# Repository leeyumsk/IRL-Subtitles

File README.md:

# IRL-Subtitles

Using techniques similar to human perception to localize sounds and speakers.

## Project Details

The final goal of the project is to make AR-Glasses that can display text taken from microphones to be displayed on a heads up display to the user. The system integrates a microphone array, and a camera to localize sound, transcribe speech, and visually present captions on a laptop screen connected to the glasses. This project would ideally be combined with a smart glass display/platform in the future.

## Current State
The current state of the project is that there is no processing that is happening locally on the board, all the data is being streamed over to a computer to be processed and displayed. There are one ESP32-S3 wroom 1U that are being used to get audio and one ESP32-S3 eye that is acting as an AP, camera, and handling the data routing. This is a battery powered data colletion unit.

## Project Structure
The project consists of:
1. [Firmware](#1-firmware)
2. [Software](#2-software)
3. [Hardware](#3-hardware)
4. [Extra Documentation](#4-extra-documentation)

Each is structured into their own folders, and sub groups.

### 1. [Firmware](/Firmware/README.md)
This is the code that is running on the ESP32. Most of the code here is for data collection and transmission. This code has two main parts, one that will go on the arm board and one that goes on the eye. This was made, built, and flashed using vscode. 

#### Requirements
- ESP32 IDF
- Target set to ESP32-S3

### 2. [Software](/Software/README.md)
This is the code that will be run on the computer to process the data that is streamed. Due to time constraints the integration of the audio localization was not included in the OpenCV and speech to text display.

### 3. [Hardware](/Hardware/README.md)
This has both the PBC and KiCad files and the glasses cad models.
The main components are:
1. Arm boards - Holds the power management and mics that collect teh audio data.
2. ESP32S3 eye - Collects the visual data and acts as an access point to route the data.
3. [PowerBoost 1000 Charger](https://www.adafruit.com/product/2465) this handle the battery.
4. Frames - Holds all components in a glasses form to be a wearable design.

#### KiCad
This has the KiCad models that were to produce the boards. That includes the schematics, the PCB files, and gerber files to order the glasses.

#### Onshape
Onshape was used to the frames that the PCBs will fit in on the glasses.

### 4. [Extra Documentation](/Extra%20Documentation/README.md)
This is all the documentation that was created in the testing and researching on creating the glasses. This also has the pin outs that were used on the glasses for reference.

## What the Project could use
1. Faster processing, moving computation on the the board.
2. Better integration between programs, face detect, sound location, and speech to text.
3. Localization of sound implemented. 
4. Battery management within code.
5. Redesign/flip the ports for the eye adapter board be able to connect to eye.

## Helpful Links
https://github.com/espressif/esp-who/tree/master

## References

[ESP-idf examples softAP](https://github.com/espressif/esp-idf/blob/master/examples/wifi/getting_started/softAP/main/softap_example_main.c)

[ESP-idf examples station](https://github.com/espressif/esp-idf/tree/master/examples/wifi/getting_started/station)

[espressif esp-who ESP32-S3-EYE](https://github.com/espressif/esp-who/blob/master/docs/en/get-started/ESP32-S3-EYE_Getting_Started_Guide.md)

[GitHub Doc](https://docs.github.com/en/get-started/writing-on-github/getting-started-with-writing-and-formatting-on-github/basic-writing-and-formatting-syntax#links)

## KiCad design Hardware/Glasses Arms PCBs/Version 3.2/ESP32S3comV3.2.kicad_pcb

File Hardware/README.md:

# Hardware
All of the hardware for the project.

## PCB

The PCB has gone through many revisions before it was eventually ordered and printed. The older version are in previous versions branch.

### Version 3.2
Version 3.2 is tha iteration that is used for this guide, where there in now only one ESP32-S3 on the sides of the frames. This has two spots to place a battery on where the battery WITH LOW BATTERY SHUTOFF to the board and on to use with a socketed BMS designed like the one from adafuit, [PowerBoost 500 Charger](https://www.adafruit.com/product/1944). The adapter for the eye has also change to pass through the audio data to the other board.

Version 3.2

These are the pin out for the arm boards.
|Right| | |Left| | 
| ------------- | ------- | - | ------- | ------------- |
| GPIO 15 | GPIO 13 (WS) | | GND | WS | 
| GPIO 9 | GPIO 14 (SCK) | | 3V3 | SCK| 
| GPIO 10 | GPIO 21 (SD) | | x | x | 
| GPIO 11 | 3V3 | | x | SDin | 
| GPIO 12 | GND | | x | LB3v3 |

Eye Adapter Board pins:
| Top | | | | | |
| ------ | ----- | ----- | ---- | ---- | ---- |
| x | x | LB3v3 | SD | SCK | WS|
| GND | IO46 | IO45 | IO3 | IO0 | 3V3 | 
| Bottom | | | | | |
| IO43 | IO21 | IO44 | IO47 | IO48 | GND |
| X | LB3v3 | SD | SCK | WS | 3V3 | 

In the hardware folder is all the production files that is needed to order the PCBs.

## Frames

The frames are designed to clip together without requiring a trip to the hardware store.
The CAD model is parametrically modeled to assist with personalization.
The CAD work was done in onshape and is publicly available.
https://cad.onshape.com/documents/a7485a7ae3b222abdb51885d/w/8202e3e3be7d45f8a3fb9981/e/ac120f3095f84bb498783c7c

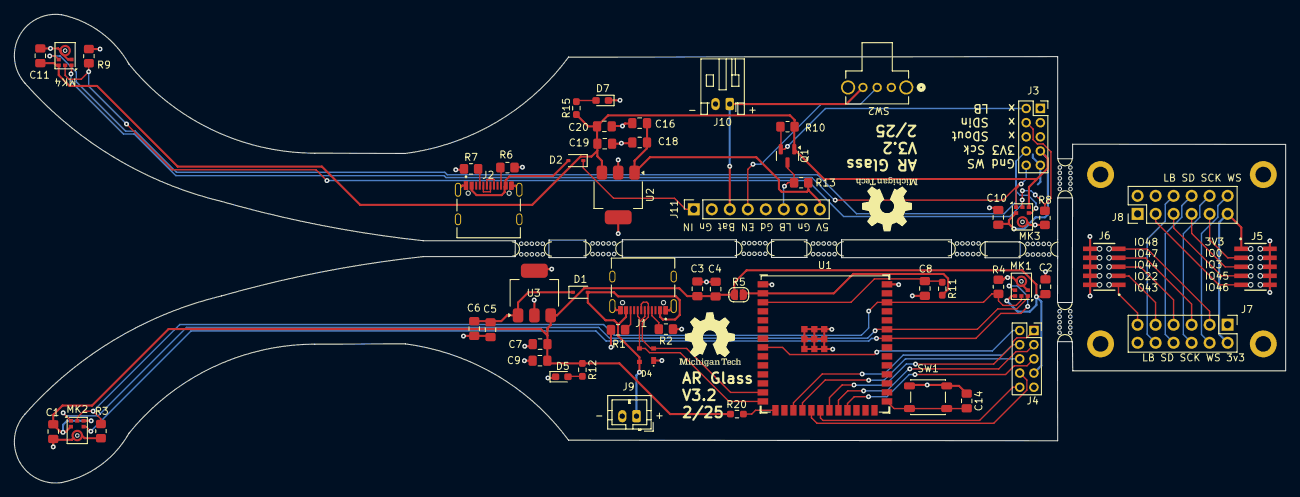
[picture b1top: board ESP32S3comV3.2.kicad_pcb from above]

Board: 2 copper layers, 179.3 x 66.1 mm, 69 parts (0 on the bottom side), 54 nets.

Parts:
C1, C2, C4, C6, C7, C10, C11, C14, C18, C19: 0.1uF; C_0805_2012Metric_Pad1.18x1.45mm_HandSolder
C3, C5, C9, C16, C20: 10uF; C_0805_2012Metric_Pad1.18x1.45mm_HandSolder
C8: 1uF; C_0805_2012Metric_Pad1.18x1.45mm_HandSolder
D1, D2: 1N5819WS; D_SOD-323
D4: PRTR5V0U2X_215; SOT143B
D5, D7: LED; LED_0603_1608Metric_Pad1.05x0.95mm_HandSolder
H1, H2, H3, H4: MountingHole_Pad_MP; MountingHole_2.2mm_M2_DIN965_Pad
J1, J2: USB_C_Receptacle_USB2.0_16P; HRO_TYPE-C-31-M-12
J3, J4: PinSocket_2x05_P2.00mm_Vertical
J5, J6: BD050-10-A-0-0500-L-D; GCT_BD050-10-A-1-0500-L-D
J7, J8: PinHeader_2x06_P2.54mm_Vertical
J9: Conn_02x01; JST_PH_B2B-PH-K_1x02_P2.00mm_Vertical
J10: Conn_01x02; JST_PH_S2B-PH-K_1x02_P2.00mm_Horizontal
J11: Conn_01x08_Socket; PinSocket_1x08_P2.54mm_Vertical
MK1, MK2, MK3, MK4: ICS-43434; InvenSense_ICS-43434-6_3.5x2.65mm
Q1: BSS138; SOT-23
R1, R2, R6, R7: 5.1K; R_0805_2012Metric_Pad1.20x1.40mm_HandSolder
R3, R4, R8, R9: 100k; R_0805_2012Metric_Pad1.20x1.40mm_HandSolder
R5: 0; SolderJumper-2_P1.3mm_Open_RoundedPad1.0x1.5mm
R10, R13: 10k; R_0805_2012Metric_Pad1.20x1.40mm_HandSolder
R11: 10K; R_0603_1608Metric_Pad0.98x0.95mm_HandSolder
R12, R15, R20: 1K; R_0603_1608Metric_Pad0.98x0.95mm_HandSolder
SW1: SW_Push; SW_SPST_PTS647_Sx38
SW2: OS102011MA1QN1; OS102011MA1QN1_CNK
U1: ESP32-S3-WROOM-1U-N8R8; ESP32-S3-WROOM-1U
U2: LT1963AxST-3.3; SOT-223-3_TabPin2
U3: LT1963AEST-3.3; SOT-223-3_TabPin2
mouse-bite-3mm-slot, mouse-bite-3mm-slot-2, mouse-bite-3mm-slot-3, mouse-bite-3mm-slot-4, mouse-bite-3mm-slot-5, mouse-bite-3mm-slot-6, mouse-bite-3mm-slot-7, mouse-bite-3mm-slot-8: 0; mouse-bite-3mm-slot

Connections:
/BoardR/5V: C16.1, C18.1, J11.8, R13.1, U2.1 (IN)
/BoardR/Bat: J10.1, J11.3, SW2.3
/BoardR/CC1: J2.A5 (CC1), R7.2
/BoardR/CC2: J2.B5 (CC2), R6.2
/BoardR/D+: J2.A6 (D+), J2.B6 (D+)
/BoardR/D-: J2.A7 (D-), J2.B7 (D-)
/BoardR/EN: J11.4, SW2.2
/BoardR/LB: J11.6, Q1.3 (D), R13.2
/BoardR/LB3v3: J3.2, Q1.2 (S), R10.2
/BoardR/SCK: J3.8, MK3.4 (SCK), MK4.4 (SCK)
/BoardR/SDin: J3.4, MK3.6 (SD), MK4.6 (SD), R8.1, R9.1
/BoardR/USB: D2.1 (K), J11.1
/BoardR/VBUS: D2.2 (A), J2.A4 (VBUS), J2.A9 (VBUS), J2.B4 (VBUS), J2.B9 (VBUS)
/BoardR/VCC_3V3: C10.1, C11.1, C19.1, C20.1, J3.7, MK3.2 (LR), MK3.5 (VDD), MK4.5 (VDD), Q1.1 (G), R10.1, R15.1, U2.3 (OUT)
/BoardR/WS: J3.10, MK3.1 (WS), MK4.1 (WS)
/CC1: J1.A5 (CC1), R2.2
/CC2: J1.B5 (CC2), R1.2
/CHIP_PU: C8.1, R11.1, U1.3 (EN)
/D+: D4.3, J1.A6 (D+), J1.B6 (D+), U1.14 (IO20)
/D-: D4.2, J1.A7 (D-), J1.B7 (D-), U1.13 (IO19)
/ESP_3V3: R5.2, R11.2, U1.2 (3V3)
/Eye connect/IO0: J5.3, J8.9
/Eye connect/IO3: J5.5, J8.7
/Eye connect/IO21: J6.3, J7.9
/Eye connect/IO43: J6.1, J7.11
/Eye connect/IO44: J6.5, J7.7
/Eye connect/IO45: J5.7, J8.5
/Eye connect/IO46: J5.9, J8.3
/Eye connect/IO47: J6.7, J7.5
/Eye connect/IO48: J6.9, J7.3
/Eye connect/LB: J7.10, J8.6
/Eye connect/SCK1: J7.6, J8.10
/Eye connect/SD1: J7.8, J8.8
/Eye connect/VCC_3V3: J5.1, J7.2, J8.11
/Eye connect/WS1: J7.4, J8.12
/GPIO0: C14.2, SW1.2, U1.27 (IO0)
/GPIO2: MK1.6 (SD), MK2.6 (SD), R3.1, R4.1, U1.38 (IO2)
/GPIO3: R20.1, U1.15 (IO3)
/GPIO9: J4.4, U1.17 (IO9)
/GPIO10: J4.6, U1.18 (IO10)
/GPIO11: J4.8, U1.19 (IO11)
/GPIO12: J4.10, U1.20 (IO12)
/GPIO13: J4.1, U1.21 (IO13)
/GPIO14: J4.3, U1.22 (IO14)
/GPIO15: J4.2, U1.8 (IO15)
/GPIO21: J4.5, U1.23 (IO21)
/GPIO41: MK1.4 (SCK), MK2.4 (SCK), U1.34 (IO41)
/GPIO42: MK1.1 (WS), MK2.1 (WS), U1.35 (IO42)
/VBUS: D1.2 (A), D4.4, J1.A4 (VBUS), J1.A9 (VBUS), J1.B4 (VBUS), J1.B9 (VBUS), J9.1
/VCC_3V3: C1.1, C2.1, C3.1, C4.1, C7.1, C9.1, J4.7, MK1.5 (VDD), MK2.2 (LR), MK2.5 (VDD), R5.1, R12.1, R20.2, U3.3 (OUT)
/VCC_5: C5.1, C6.1, D1.1 (K), U3.1 (IN)
GND: C1.2, C2.2, C3.2, C4.2, C5.2, C6.2, C7.2, C8.2, C9.2, C10.2, C11.2, C14.1, C16.2, C18.2, C19.2, C20.2, D4.1, D5.1 (K), D7.1 (K), J1.A1 (GND), J1.A12 (GND), J1.B1 (GND), J1.B12 (GND), J1.S1 (SHIELD), J2.A1 (GND), J2.A12 (GND), J2.B1 (GND), J2.B12 (GND), J2.S1 (SHIELD), J3.9, J4.9, J5.2, J5.4, J5.6, J5.8, J5.10, J6.2, J6.4, J6.6, J6.8, J6.10, J7.1, J8.1, J9.2, J10.2, J11.2, J11.5, J11.7, MK1.2 (LR), MK1.3 (GND), MK2.3 (GND), MK3.3 (GND), MK4.2 (LR), MK4.3 (GND), R1.1, R2.1, R3.2, R4.2, R6.1, R7.1, R8.2, R9.2, SW1.1, SW2.1, U1.1 (GND), U1.40 (GND), U1.41 (GND), U2.2 (GND), U3.2 (GND)
unnamed: D5.2 (A), R12.2
unnamed: D7.2 (A), R15.2

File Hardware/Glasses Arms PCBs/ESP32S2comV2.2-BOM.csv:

Designator,Footprint,Quantity,Value,LCSC Part #
"C1, C10, C11, C13, C2, C4, C6, C7",0805,8,0.1uF,C49678
"C12, C3, C5, C9",0805,4,10uF,C15850
"C17, C8",0805,2,1uF,C89378
"D1, D2",D_SOD-323,2,1N5819WS,C191023
"D3, D4",SOT143B,2,PRTR5V0U2X_215,C2827688
"D5, D6",0603,2,LED,C2286
"J1, J2",HRO_TYPE-C-31-M-12,2,USB_C_Receptacle_USB2.0_16P,C165948
"J3, J4",PinSocket_2x05_P2.00mm_Vertical,2,Connector_Generic:Conn_02x05_Top_Bottom,C225304
"MK1, MK2, MK3, MK4",InvenSense_ICS-43434-6_3.5x2.65mm,4,ICS-43434,
"MOUSE-BITE-3MM-SLOT, MOUSE-BITE-3MM-SLOT-2, MOUSE-BITE-3MM-SLOT-3, MOUSE-BITE-3MM-SLOT-4, MOUSE-BITE-3MM-SLOT-5, MOUSE-BITE-3MM-SLOT-6",mouse-bite-3mm-slot,6,0,
"R1, R2, R6, R7",0805,4,5.1K,C27834
"R10, R5",SolderJumper-2_P1.3mm_Open_RoundedPad1.0x1.5mm,2,0,
"R11, R13",0603,2,10K,C25804
"R12, R14, R20, R21",0603,4,1K,C21190
"R3, R4, R8, R9",0805,4,100k,C149504
"U1, U8",ESP32-S3-WROOM-1U,2,ESP32-S3-WROOM-1U-N8R8,C2980300
U3,SOT-223-3_TabPin2,1,LT1963AxST-3.3,C459918

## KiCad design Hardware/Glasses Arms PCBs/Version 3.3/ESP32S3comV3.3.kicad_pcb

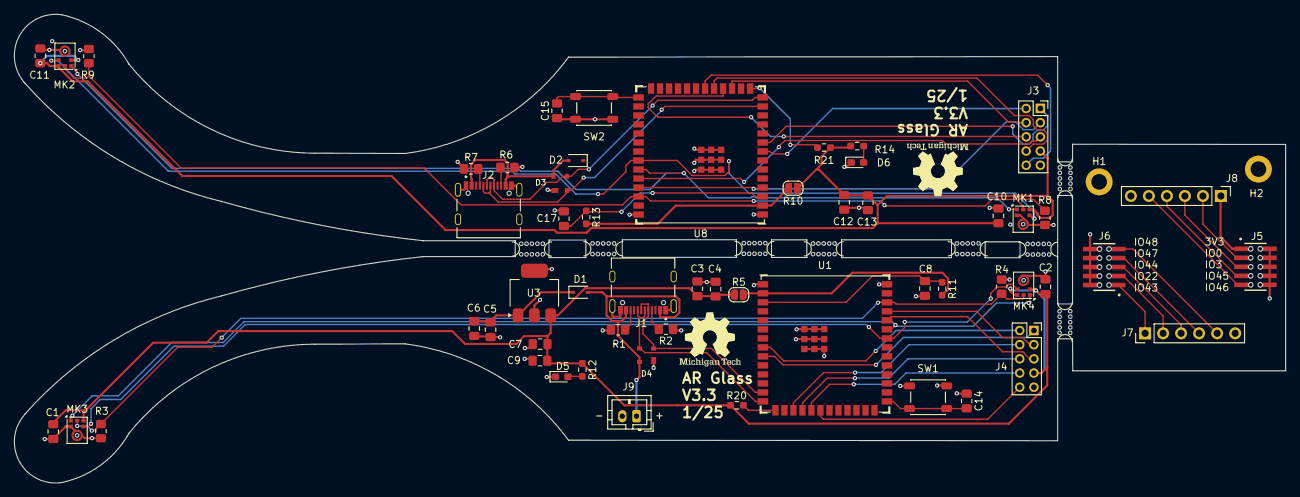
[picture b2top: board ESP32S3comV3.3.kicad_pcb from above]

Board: 2 copper layers, 179.3 x 66.1 mm, 66 parts (0 on the bottom side), 56 nets.

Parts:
C1, C2, C4, C6, C7, C10, C11, C13, C14, C15: 0.1uF; C_0805_2012Metric_Pad1.18x1.45mm_HandSolder
C3, C5, C9, C12: 10uF; C_0805_2012Metric_Pad1.18x1.45mm_HandSolder
C8, C17: 1uF; C_0805_2012Metric_Pad1.18x1.45mm_HandSolder
D1, D2: 1N5819WS; D_SOD-323
D3, D4: PRTR5V0U2X_215; SOT143B
D5, D6: LED; LED_0603_1608Metric_Pad1.05x0.95mm_HandSolder
H1, H2: MountingHole_Pad_MP; MountingHole_2.2mm_M2_DIN965_Pad
J1, J2: USB_C_Receptacle_USB2.0_16P; HRO_TYPE-C-31-M-12
J3, J4: Connector_Generic:Conn_02x05_Top_Bottom; PinSocket_2x05_P2.00mm_Vertical
J5, J6: BD050-10-A-0-0500-L-D; GCT_BD050-10-A-1-0500-L-D
J7, J8: Conn_01x06; PinHeader_1x06_P2.54mm_Vertical
J9: Conn_02x01; JST_PH_B2B-PH-K_1x02_P2.00mm_Vertical
MK1, MK2, MK3, MK4: ICS-43434; InvenSense_ICS-43434-6_3.5x2.65mm
R1, R2, R6, R7: 5.1K; R_0805_2012Metric_Pad1.20x1.40mm_HandSolder
R3, R4, R8, R9: 100k; R_0805_2012Metric_Pad1.20x1.40mm_HandSolder
R5, R10: 0; SolderJumper-2_P1.3mm_Open_RoundedPad1.0x1.5mm
R11, R13: 10K; R_0603_1608Metric_Pad0.98x0.95mm_HandSolder
R12, R14, R20, R21: 1K; R_0603_1608Metric_Pad0.98x0.95mm_HandSolder
SW1, SW2: SW_Push; SW_SPST_PTS647_Sx38
U1, U8: ESP32-S3-WROOM-1U-N8R8; ESP32-S3-WROOM-1U
U3: LT1963AxST-3.3; SOT-223-3_TabPin2
mouse-bite-3mm-slot, mouse-bite-3mm-slot-2, mouse-bite-3mm-slot-3, mouse-bite-3mm-slot-4, mouse-bite-3mm-slot-5, mouse-bite-3mm-slot-6, mouse-bite-3mm-slot-6#2, mouse-bite-3mm-slot-6#3: 0; mouse-bite-3mm-slot

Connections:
/BoardR/CC1: J2.A5 (CC1), R7.2
/BoardR/CC2: J2.B5 (CC2), R6.2
/BoardR/CHIP_PU: C17.1, R13.1, U8.3 (EN)
/BoardR/D+: D3.3, J2.A6 (D+), J2.B6 (D+), U8.14 (IO20)
/BoardR/D-: D3.2, J2.A7 (D-), J2.B7 (D-), U8.13 (IO19)
/BoardR/ESP_3V3: R10.2, R13.2, U8.2 (3V3)
/BoardR/GPIO0: C15.2, SW2.2, U8.27 (IO0)
/BoardR/GPIO2: MK1.6 (SD), MK2.6 (SD), R8.1, R9.1, U8.38 (IO2)
/BoardR/GPIO3: R21.1, U8.15 (IO3)
/BoardR/GPIO9: J3.4, U8.17 (IO9)
/BoardR/GPIO10: J3.6, U8.18 (IO10)
/BoardR/GPIO11: J3.8, U8.19 (IO11)
/BoardR/GPIO12: J3.10, U8.20 (IO12)
/BoardR/GPIO15: J3.2, U8.8 (IO15)
/BoardR/GPIO16: J3.1, U8.9 (IO16)
/BoardR/GPIO41: MK1.4 (SCK), MK2.4 (SCK), U8.34 (IO41)
/BoardR/GPIO42: MK1.1 (WS), MK2.1 (WS), U8.35 (IO42)
/BoardR/RXD0: J3.5, U8.36 (RXD0)
/BoardR/TXD0: J3.3, U8.37 (TXD0)
/BoardR/VBUS: D2.2 (A), D3.4, J2.A4 (VBUS), J2.A9 (VBUS), J2.B4 (VBUS), J2.B9 (VBUS)
/BoardR/VCC_3V3: C10.1, C11.1, C12.1, C13.1, J3.7, MK1.5 (VDD), MK2.2 (LR), MK2.5 (VDD), R10.1, R14.1, R21.2
/CC1: J1.A5 (CC1), R2.2
/CC2: J1.B5 (CC2), R1.2
/CHIP_PU: C8.1, R11.1, U1.3 (EN)
/D+: D4.3, J1.A6 (D+), J1.B6 (D+), U1.14 (IO20)
/D-: D4.2, J1.A7 (D-), J1.B7 (D-), U1.13 (IO19)
/ESP_3V3: R5.2, R11.2, U1.2 (3V3)
/Eye connect/IO0: J5.3, J8.2
/Eye connect/IO3: J5.5, J8.3
/Eye connect/IO21: J6.3, J7.2
/Eye connect/IO43: J6.1, J7.1
/Eye connect/IO44: J6.5, J7.3
/Eye connect/IO45: J5.7, J8.4
/Eye connect/IO46: J5.9, J8.5
/Eye connect/IO47: J6.7, J7.4
/Eye connect/IO48: J6.9, J7.5
/Eye connect/VCC_3V3: J5.1, J8.1
/GPIO0: C14.2, SW1.2, U1.27 (IO0)
/GPIO2: MK3.6 (SD), MK4.6 (SD), R3.1, R4.1, U1.38 (IO2)
/GPIO3: R20.1, U1.15 (IO3)
/GPIO9: J4.4, U1.17 (IO9)
/GPIO10: J4.6, U1.18 (IO10)
/GPIO11: J4.8, U1.19 (IO11)
/GPIO12: J4.10, U1.20 (IO12)
/GPIO15: J4.2, U1.8 (IO15)
/GPIO16: J4.1, U1.9 (IO16)
/GPIO41: MK3.4 (SCK), MK4.4 (SCK), U1.34 (IO41)
/GPIO42: MK3.1 (WS), MK4.1 (WS), U1.35 (IO42)
/RXD0: J4.5, U1.36 (RXD0)
/TXD0: J4.3, U1.37 (TXD0)
/VBUS: D1.2 (A), D4.4, J1.A4 (VBUS), J1.A9 (VBUS), J1.B4 (VBUS), J1.B9 (VBUS), J9.1
/VCC_3V3: C1.1, C2.1, C3.1, C4.1, C7.1, C9.1, J4.7, MK3.5 (VDD), MK4.2 (LR), MK4.5 (VDD), R5.1, R12.1, R20.2, U3.3 (OUT)
/VCC_5: C5.1, C6.1, D1.1 (K), U3.1 (IN)
GND: C1.2, C2.2, C3.2, C4.2, C5.2, C6.2, C7.2, C8.2, C9.2, C10.2, C11.2, C12.2, C13.2, C14.1, C15.1, C17.2, D3.1, D4.1, D5.1 (K), D6.1 (K), J1.A1 (GND), J1.A12 (GND), J1.B1 (GND), J1.B12 (GND), J1.S1 (SHIELD), J2.A1 (GND), J2.A12 (GND), J2.B1 (GND), J2.B12 (GND), J2.S1 (SHIELD), J3.9, J4.9, J5.2, J5.4, J5.6, J5.8, J5.10, J6.2, J6.4, J6.6, J6.8, J6.10, J7.6, J8.6, J9.2, MK1.2 (LR), MK1.3 (GND), MK2.3 (GND), MK3.2 (LR), MK3.3 (GND), MK4.3 (GND), R1.1, R2.1, R3.2, R4.2, R6.1, R7.1, R8.2, R9.2, SW1.1, SW2.1, U1.1 (GND), U1.40 (GND), U1.41 (GND), U3.2 (GND), U8.1 (GND), U8.40 (GND), U8.41 (GND)
unnamed: D5.2 (A), R12.2
unnamed: D6.2 (A), R14.2

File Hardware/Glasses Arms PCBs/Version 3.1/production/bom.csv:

Designator,Footprint,Quantity,Value,LCSC Part #
"C1, C10, C11, C14, C18, C19, C2, C4, C6, C7",0805,10,0.1uF,
"C16, C20, C3, C5, C9",0805,5,10uF,
C8,0805,1,1uF,
"D1, D2",D_SOD-323,2,1N5819WS,
D4,SOT143B,1,PRTR5V0U2X_215,
"D5, D7",0603,2,LED,
"J1, J2",HRO_TYPE-C-31-M-12,2,USB_C_Receptacle_USB2.0_16P,
J10,JST_PH_S2B-PH-K_1x02_P2.00mm_Horizontal,1,Conn_01x02,
J11,PinSocket_1x08_P2.54mm_Vertical,1,Conn_01x08_Socket,
"J3, J4",PinSocket_2x05_P2.00mm_Vertical,2,Connector_Generic:Conn_02x05_Top_Bottom,
"J5, J6",GCT_BD050-10-A-1-0500-L-D,2,BD050-10-A-0-0500-L-D,
"J7, J8",PinHeader_2x06_P2.54mm_Vertical,2,Conn_02x06,
J9,JST_PH_B2B-PH-K_1x02_P2.00mm_Vertical,1,Conn_02x01,
"MK1, MK2, MK5, MK6",MIC_CMM-4030D-261-I2S-TR,4,MSM261S4030H0R,
"MOUSE-BITE-3MM-SLOT, MOUSE-BITE-3MM-SLOT-2, MOUSE-BITE-3MM-SLOT-3, MOUSE-BITE-3MM-SLOT-4, MOUSE-BITE-3MM-SLOT-5, MOUSE-BITE-3MM-SLOT-6, MOUSE-BITE-3MM-SLOT-7, MOUSE-BITE-3MM-SLOT-8",mouse-bite-3mm-slot,8,0,
Q1,SOT-23,1,BSS138,
"R1, R2, R6, R7",0805,4,5.1K,
"R10, R13",0805,2,10k,
R11,0603,1,10K,
"R12, R15, R20",0603,3,1K,
"R3, R4, R8, R9",0805,4,100k,
R5,SolderJumper-2_P1.3mm_Open_RoundedPad1.0x1.5mm,1,0,
SW1,SW_SPST_PTS647_Sx38,1,SW_Push,
SW2,OS102011MA1QN1_CNK,1,OS102011MA1QN1,
U1,ESP32-S3-WROOM-1U,1,ESP32-S3-WROOM-1U-N8R8,
"U2, U3",SOT-223-3_TabPin2,2,LT1963AxST-3.3,

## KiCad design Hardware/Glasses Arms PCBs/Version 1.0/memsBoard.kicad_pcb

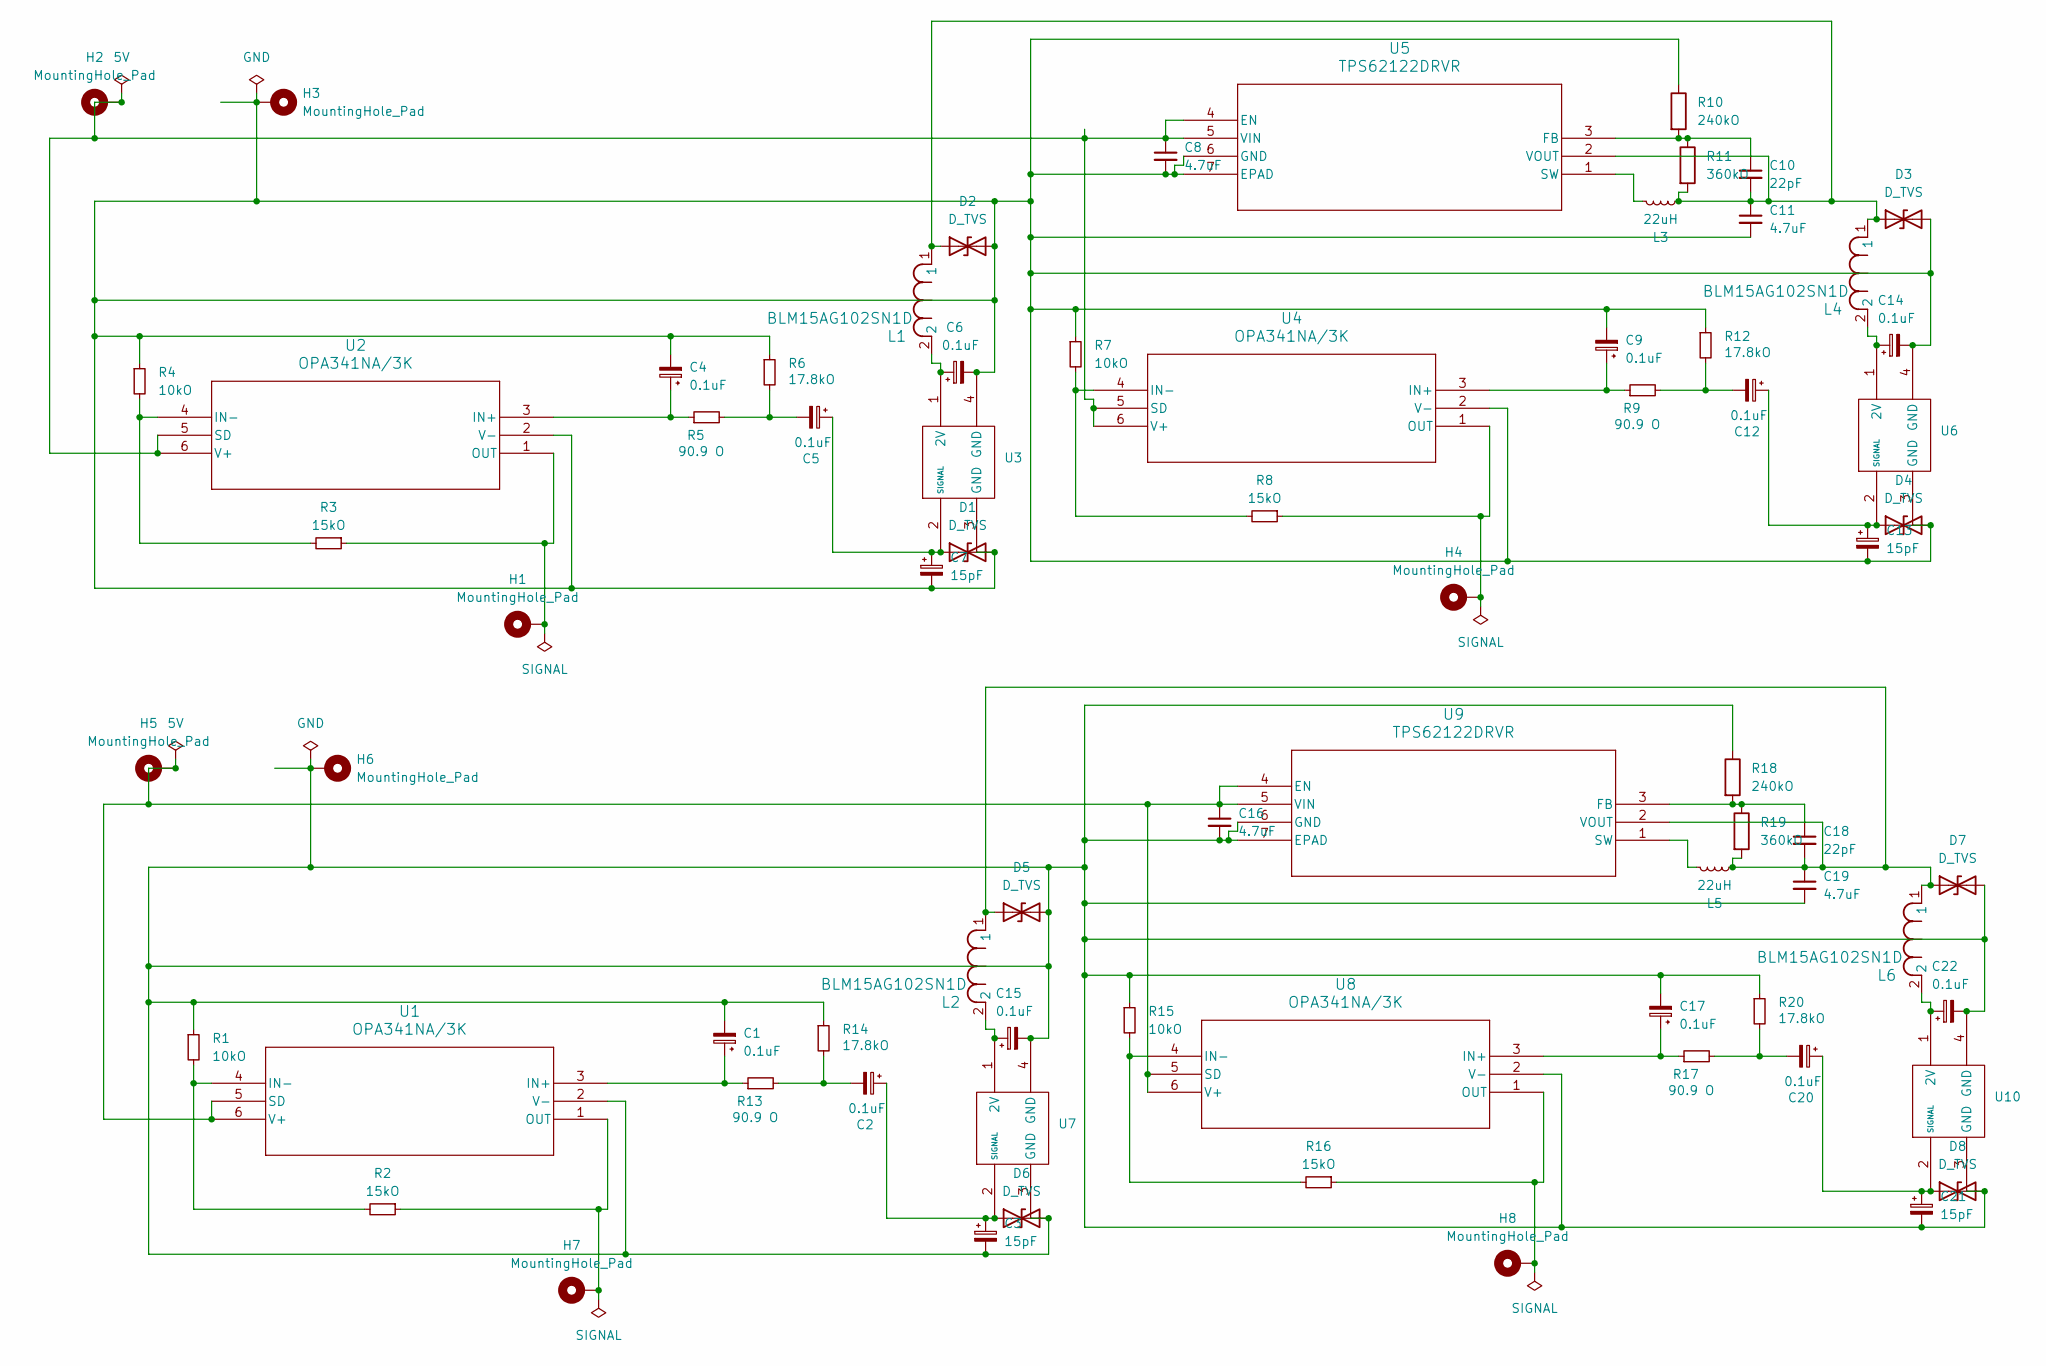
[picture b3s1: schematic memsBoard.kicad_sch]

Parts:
C1, C2, C4, C5, C6, C9, C12, C14, C15, C17, C20, C22: 0.1uF; CAPMP3.4X1.6_1.8N_KEM
C3, C7, C13, C21: 15pF; CAPC0603X33N
C8, C11, C16, C19: 4.7uF; TAJA_AVX
C10, C18: 22pF; G-033_MUR
D1, D2, D3, D4, D5, D6, D7, D8: D_TVS; D_SOD-882D
H1, H2, H3, H4, H5, H6, H7, H8: MountingHole_Pad; SolderWire-0.15sqmm_1x01_D0.5mm_OD1.5mm
L1, L2, L4, L6: BLM15AG102SN1D; IND_BLM15_0402_MUR
L3, L5: 22uH; IND_2012_TDK
R1, R4, R7, R15: 10kO; RC0402N_PAN
R2, R3, R8, R16: 15kO; RC0402N_PAN
R5, R9, R13, R17: 90.9 O; RES_RMCF2512_STP
R6, R12, R14, R20: 17.8kO; RES_RN73R_1E_KOA
R10, R18: 240kO; RC0402N_PAN
R11, R19: 360kO; RC0402N_PAN
U1, U2, U4, U8: OPA341NA/3K; DBV6
U3, U6, U7, U10: CMM2718AT
U5, U9: TPS62122DRVR; DRV6_1P6X1

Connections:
unnamed: C2.2, R13.2, R14.2
unnamed: C5.2, R5.2, R6.2
unnamed: C12.2, R9.2, R12.2
unnamed: C20.2, R17.2, R20.2
unnamed: C5.1, C7.1, D1.1 (A1), U3.2 (SIGNAL)
unnamed: C4.2, C6.2, C7.2, C8.2, C9.2, C11.2, C13.2, C14.2, D1.2 (A2), D2.2 (A2), D3.2 (A2), D4.2 (A2), H3.1, R4.1, R6.1, R7.1, R10.1, R12.1, U2.2 (V-), U3.3 (GND), U3.4 (GND), U4.2 (V-), U5.6 (GND), U5.7 (EPAD), U6.3 (GND), U6.4 (GND)
unnamed: C10.2, C11.1, D2.1 (A1), D3.1 (A1), L1.1, L3.1, L4.1, R11.2, U5.2 (VOUT)
unnamed: C12.1, C13.1, D4.1 (A1), U6.2 (SIGNAL)
unnamed: C18.2, C19.1, D5.1 (A1), D7.1 (A1), L2.1, L5.1, L6.1, R19.2, U9.2 (VOUT)
unnamed: C1.2, C3.2, C15.2, C16.2, C17.2, C19.2, C21.2, C22.2, D5.2 (A2), D6.2 (A2), D7.2 (A2), D8.2 (A2), H6.1, R1.1, R14.1, R15.1, R18.1, R20.1, U1.2 (V-), U7.3 (GND), U7.4 (GND), U8.2 (V-), U9.6 (GND), U9.7 (EPAD), U10.3 (GND), U10.4 (GND)
unnamed: C2.1, C3.1, D6.1 (A1), U7.2 (SIGNAL)
unnamed: C20.1, C21.1, D8.1 (A1), U10.2 (SIGNAL)
unnamed: C1.1, R13.1, U1.3 (IN+)
unnamed: R1.2, R2.2, U1.4 (IN-)
unnamed: H7.1, R2.1, U1.1 (OUT)
unnamed: C16.1, H5.1, U1.5 (SD), U1.6 (V+), U8.5 (SD), U8.6 (V+), U9.4 (EN), U9.5 (VIN)
unnamed: C4.1, R5.1, U2.3 (IN+)
unnamed: R3.2, R4.2, U2.4 (IN-)
unnamed: H1.1, R3.1, U2.1 (OUT)
unnamed: C8.1, H2.1, U2.5 (SD), U2.6 (V+), U4.5 (SD), U4.6 (V+), U5.4 (EN), U5.5 (VIN)
unnamed: C6.1, L1.2, U3.1 (2V)
unnamed: C9.1, R9.1, U4.3 (IN+)
unnamed: R7.2, R8.2, U4.4 (IN-)
unnamed: H4.1, R8.1, U4.1 (OUT)
unnamed: C10.1, R10.2, R11.1, U5.3 (FB)
unnamed: L3.2, U5.1 (SW)
unnamed: C14.1, L4.2, U6.1 (2V)
unnamed: C15.1, L2.2, U7.1 (2V)
unnamed: C17.1, R17.1, U8.3 (IN+)
unnamed: R15.2, R16.2, U8.4 (IN-)
unnamed: H8.1, R16.1, U8.1 (OUT)
unnamed: C18.1, R18.2, R19.1, U9.3 (FB)
unnamed: L5.2, U9.1 (SW)
unnamed: C22.1, L6.2, U10.1 (2V)

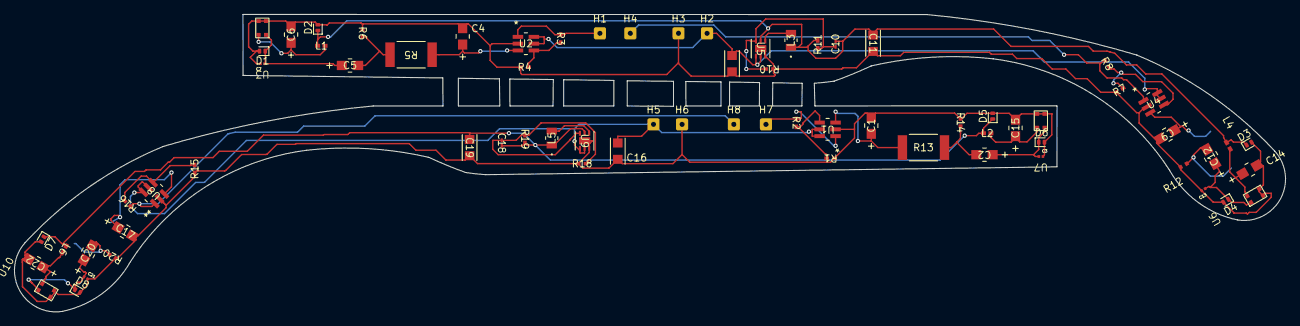
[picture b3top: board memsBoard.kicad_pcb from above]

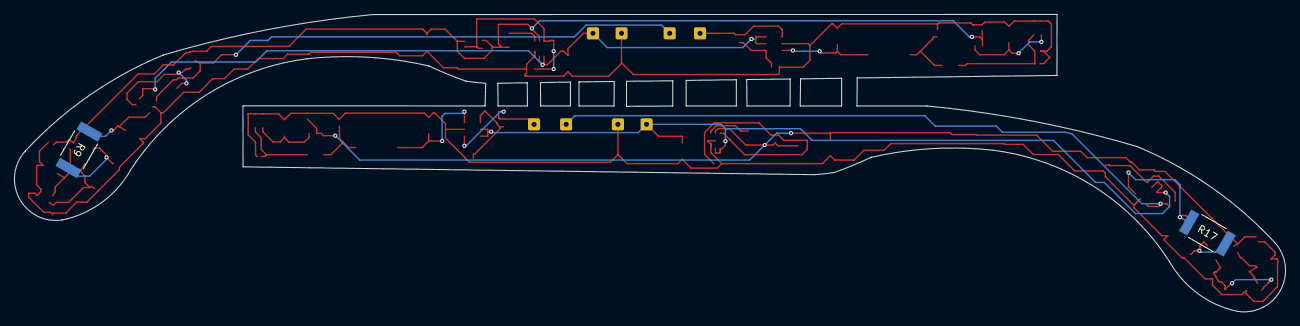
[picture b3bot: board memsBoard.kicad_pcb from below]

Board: 2 copper layers, 178.0 x 41.6 mm, 74 parts (2 on the bottom side), 34 nets.

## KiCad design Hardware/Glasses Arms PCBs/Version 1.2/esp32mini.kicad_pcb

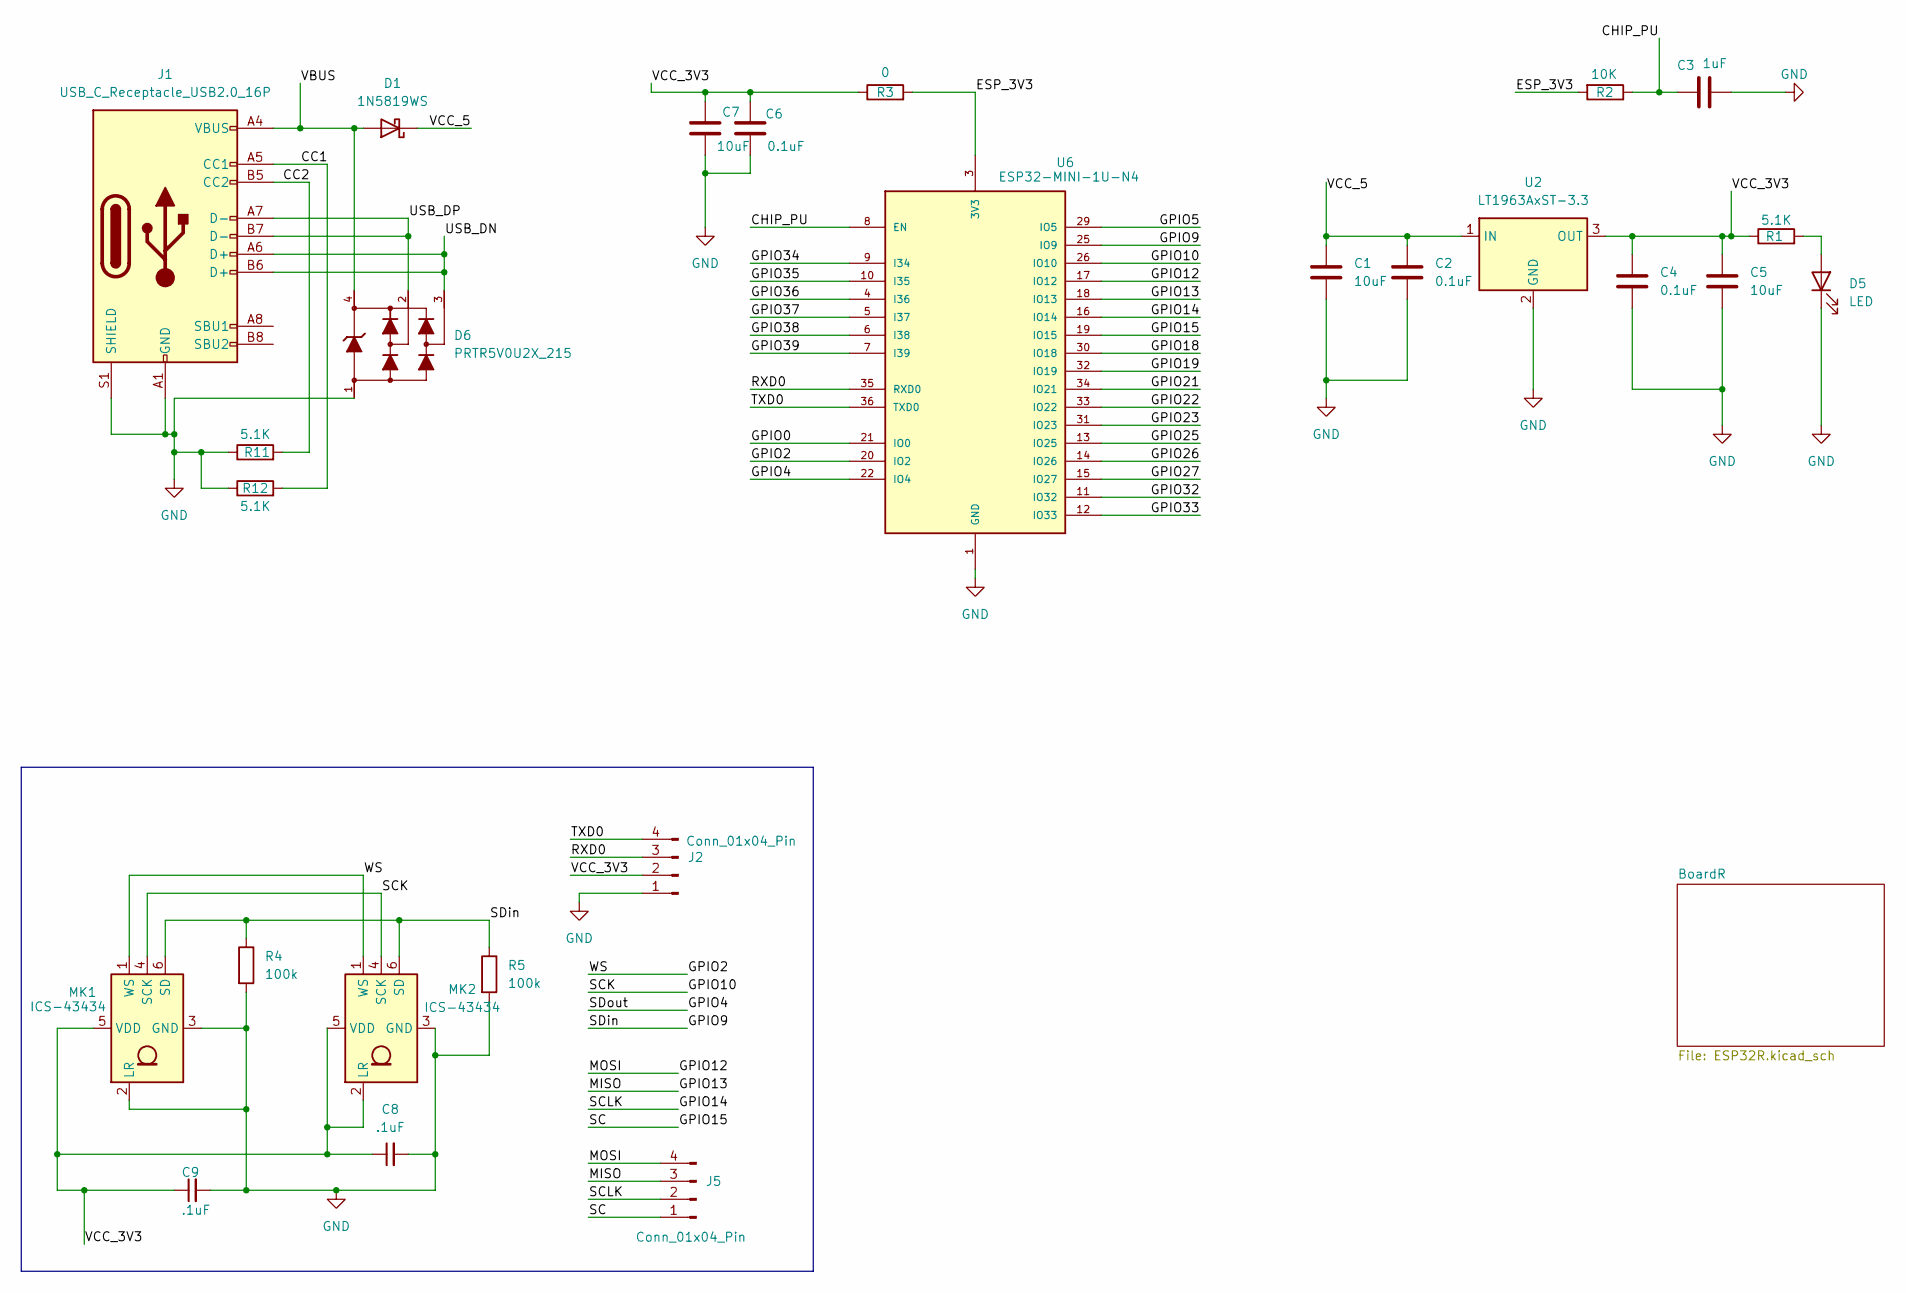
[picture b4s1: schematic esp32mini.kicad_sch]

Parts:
C1, C5, C7: 10uF; C_0805_2012Metric_Pad1.18x1.45mm_HandSolder
C2, C4, C6: 0.1uF; C_0805_2012Metric_Pad1.18x1.45mm_HandSolder
C3: 1uF; C_0805_2012Metric_Pad1.18x1.45mm_HandSolder
C8, C9: .1uF; C_0805_2012Metric_Pad1.18x1.45mm_HandSolder
D1: 1N5819WS; D_SOD-323
D5: LED; LED_0603_1608Metric_Pad1.05x0.95mm_HandSolder
D6: PRTR5V0U2X_215; SOT143B
J1: USB_C_Receptacle_USB2.0_16P; USB_C_Receptacle_JAE_DX07S016JA1R1500
J2, J5: Conn_01x04_Pin; PinHeader_1x04_P1.27mm_Vertical
MK1, MK2: ICS-43434; InvenSense_ICS-43434-6_3.5x2.65mm
R1: 5.1K; R_0603_1608Metric_Pad0.98x0.95mm_HandSolder
R2: 10K; R_0805_2012Metric
R3: 0; SolderJumper-2_P1.3mm_Open_RoundedPad1.0x1.5mm
R4, R5: 100k; R_0805_2012Metric_Pad1.20x1.40mm_HandSolder
R11, R12: 5.1K; R_0805_2012Metric_Pad1.20x1.40mm_HandSolder
U2: LT1963AxST-3.3; DCY0004A_N
U6: ESP32-MINI-1U-N4; MODULE_ESP32-MINI-1U-N4; PARTREV v1.2

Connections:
/CC1: J1.A5 (CC1), R12.2
/CC2: J1.B5 (CC2), R11.2
/CHIP_PU: C3.1, R2.1, U6.8 (EN)
/D+: D6.3, J1.A6 (D+), J1.B6 (D+)
/D-: D6.2, J1.A7 (D-), J1.B7 (D-)
/ESP_3V3: R2.2, R3.2, U6.3 (3V3)
/GPIO0: U6.21 (IO0)
/GPIO2: MK1.1 (WS), MK2.1 (WS), U6.20 (IO2)
/GPIO4: U6.22 (IO4)
/GPIO5: U6.29 (IO5)
/GPIO9: MK1.6 (SD), MK2.6 (SD), R4.1, R5.1, U6.25 (IO9)
/GPIO10: MK1.4 (SCK), MK2.4 (SCK), U6.26 (IO10)
/GPIO12: J5.4, U6.17 (IO12)
/GPIO13: J5.3, U6.18 (IO13)
/GPIO14: J5.2, U6.16 (IO14)
/GPIO15: J5.1, U6.19 (IO15)
/GPIO18: U6.30 (IO18)
/GPIO19: U6.32 (IO19)
/GPIO21: U6.34 (IO21)
/GPIO22: U6.33 (IO22)
/GPIO23: U6.31 (IO23)
/GPIO25: U6.13 (IO25)
/GPIO26: U6.14 (IO26)
/GPIO27: U6.15 (IO27)
/GPIO32: U6.11 (IO32)
/GPIO33: U6.12 (IO33)
/GPIO34: U6.9 (I34)
/GPIO35: U6.10 (I35)
/GPIO36: U6.4 (I36)
/GPIO37: U6.5 (I37)
/GPIO38: U6.6 (I38)
/GPIO39: U6.7 (I39)
/RXD0: J2.3, U6.35 (RXD0)
/TXD0: J2.4, U6.36 (TXD0)
/VBUS: D1.2 (A), D6.4, J1.A4 (VBUS), J1.A9 (VBUS), J1.B4 (VBUS), J1.B9 (VBUS)
/VCC_3V3: C4.1, C5.1, C6.1, C7.1, C8.1, C9.1, J2.2, MK1.5 (VDD), MK2.2 (LR), MK2.5 (VDD), R1.1, R3.1, U2.3 (OUT)
/VCC_5: C1.1, C2.1, D1.1 (K), U2.1 (IN)
GND: C1.2, C2.2, C3.2, C4.2, C5.2, C6.2, C7.2, C8.2, C9.2, D5.1 (K), D6.1, J1.A1 (GND), J1.A12 (GND), J1.B1 (GND), J1.B12 (GND), J1.S1 (SHIELD), J2.1, MK1.2 (LR), MK1.3 (GND), MK2.3 (GND), R4.2, R5.2, R11.1, R12.1, U2.2 (GND), U6.1 (GND), U6.2 (GND), U6.27 (GND), U6.38 (GND), U6.39 (GND), U6.40 (GND), U6.41 (GND), U6.42 (GND), U6.43 (GND), U6.44 (GND), U6.45 (GND), U6.46 (GND), U6.47 (GND), U6.48 (GND), U6.49 (GND), U6.50 (GND), U6.51 (GND), U6.52 (GND), U6.53 (GND), U6.54 (GND), U6.55 (GND), U6.56 (GND), U6.57 (GND), U6.58 (GND), U6.59 (GND), U6.60 (GND), U6.61 (GND), U6.62 (GND); also elsewhere on the board
unnamed: D5.2 (A), R1.2
